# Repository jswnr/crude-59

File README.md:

# Crude-59
A 59-key USB keyboard built using Raspberry Pi Pico

## Images

## Default layout
|         |       |       |       |       |       |       |       |       |       |        |       |                  |
|---------|-------|-------|-------|-------|-------|-------|-------|-------|-------|--------|-------|------------------|
| \`~     | 1! F1 | 2@ F2 | 3# F3 | 4$ F4 | 5% F5 | 6^ F6 | 7& F7 | 8* F8 | 9( F9 | 0) F10 |       |                  |
| Tab     | Q     | W ↑   | E     | R     | T     | Y     | U     | I     | O     | P  F11 |       |                  |
| Esc     | A ←   | S ↓   | D →   | F     | G     | H     | J     | K     | L     | ;: F12 |       |                  | 
| Shift   | Z     | X     | C     | V     | B     | N     | M     | ,<    | .>    | '"     | Enter | Backspace Delete |
| Control | Super | Fn    | Alt   | Space | Space | Alt   | [{    | ]}    | /?    | \\\|   | -_    | =+               |

## Bill of materials
| Name                   | Details                          | Quantity |
|------------------------|----------------------------------|----------|
| 3D printing filament   | PLA was used                     | A/R      |
| Solder                 |                                  | A/R      |
| PCB                    | 1.2 mm thickness                 | 1        |
| Raspberry Pi Pico      |                                  | 1        |
| USB-A to Micro-B cable |                                  | 1        |
| Male pin header        | 2.54 mm pitch, 20 pins           | 2        |
| M2 screw               | Pan head, 6 mm long              | 8        |
| M2 brass insert        | 6 mm long, 3.5 mm outer diameter | 8        |
| Cherry MX switch       |                                  | 59       |
| 1N4148 diode           |                                  | 59       |

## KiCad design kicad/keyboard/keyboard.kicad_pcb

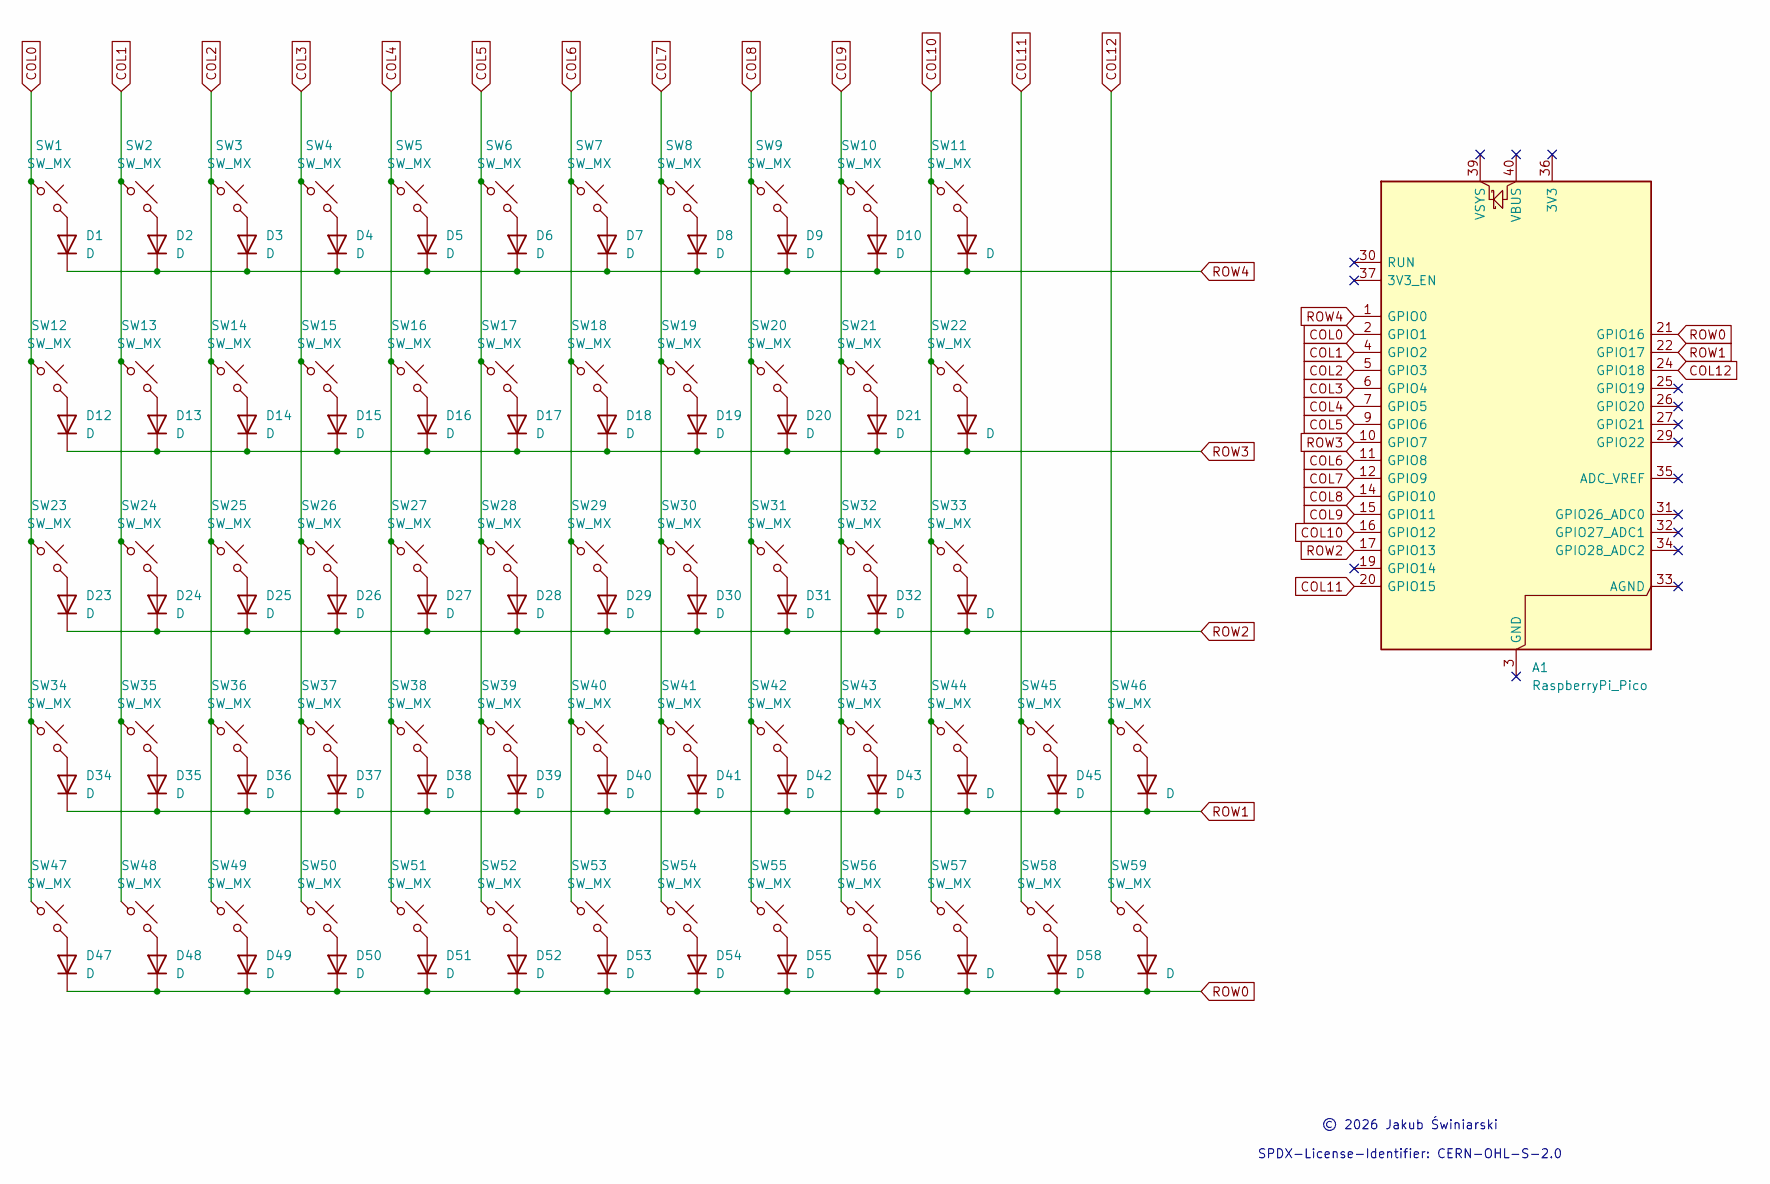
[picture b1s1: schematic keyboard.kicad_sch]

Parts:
A1: RaspberryPi_Pico; RaspberryPi_Pico_Common_THT
D1, D2, D3, D4, D5, D6, D7, D8, D9, D10, D11, D12, D13, D14, D15, D16, D17, D18, D19, D20, D21, D22, D23, D24, D25, D26, D27, D28, D29, D30, D31, D32, D33, D34, D35, D36, D37, D38, D39, D40, D41, D42, D43, D44, D45, D46, D47, D48, D49, D50, D51, D52, D53, D54, D55, D56, D57, D58, D59: D; D_DO-35_SOD27_P7.62mm_Horizontal
SW1, SW2, SW3, SW4, SW5, SW6, SW7, SW8, SW9, SW10, SW11, SW12, SW13, SW14, SW15, SW16, SW17, SW18, SW19, SW20, SW21, SW22, SW23, SW24, SW25, SW26, SW27, SW28, SW29, SW30, SW31, SW32, SW33, SW34, SW35, SW36, SW37, SW38, SW39, SW40, SW41, SW42, SW43, SW44, SW45, SW46, SW47, SW48, SW49, SW50, SW51, SW52, SW53, SW54, SW55, SW56, SW57, SW58, SW59: SW_MX; SW_Cherry_MX_1.00u_PCB

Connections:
COL0: A1.2 (GPIO1), SW1.1, SW12.1, SW23.1, SW34.1, SW47.1
COL1: A1.4 (GPIO2), SW2.1, SW13.1, SW24.1, SW35.1, SW48.1
COL2: A1.5 (GPIO3), SW3.1, SW14.1, SW25.1, SW36.1, SW49.1
COL3: A1.6 (GPIO4), SW4.1, SW15.1, SW26.1, SW37.1, SW50.1
COL4: A1.7 (GPIO5), SW5.1, SW16.1, SW27.1, SW38.1, SW51.1
COL5: A1.9 (GPIO6), SW6.1, SW17.1, SW28.1, SW39.1, SW52.1
COL6: A1.11 (GPIO8), SW7.1, SW18.1, SW29.1, SW40.1, SW53.1
COL7: A1.12 (GPIO9), SW8.1, SW19.1, SW30.1, SW41.1, SW54.1
COL8: A1.14 (GPIO10), SW9.1, SW20.1, SW31.1, SW42.1, SW55.1
COL9: A1.15 (GPIO11), SW10.1, SW21.1, SW32.1, SW43.1, SW56.1
COL10: A1.16 (GPIO12), SW11.1, SW22.1, SW33.1, SW44.1, SW57.1
COL11: A1.20 (GPIO15), SW45.1, SW58.1
COL12: A1.24 (GPIO18), SW46.1, SW59.1
unnamed: D1.2 (A), SW1.2
unnamed: D2.2 (A), SW2.2
unnamed: D3.2 (A), SW3.2
unnamed: D4.2 (A), SW4.2
unnamed: D5.2 (A), SW5.2
unnamed: D6.2 (A), SW6.2
unnamed: D7.2 (A), SW7.2
unnamed: D8.2 (A), SW8.2
unnamed: D9.2 (A), SW9.2
unnamed: D10.2 (A), SW10.2
unnamed: D11.2 (A), SW11.2
unnamed: D12.2 (A), SW12.2
unnamed: D13.2 (A), SW13.2
unnamed: D14.2 (A), SW14.2
unnamed: D15.2 (A), SW15.2
unnamed: D16.2 (A), SW16.2
unnamed: D17.2 (A), SW17.2
unnamed: D18.2 (A), SW18.2
unnamed: D19.2 (A), SW19.2
unnamed: D20.2 (A), SW20.2
unnamed: D21.2 (A), SW21.2
unnamed: D22.2 (A), SW22.2
unnamed: D23.2 (A), SW23.2
unnamed: D24.2 (A), SW24.2
unnamed: D25.2 (A), SW25.2
unnamed: D26.2 (A), SW26.2
unnamed: D27.2 (A), SW27.2
unnamed: D28.2 (A), SW28.2
unnamed: D29.2 (A), SW29.2
unnamed: D30.2 (A), SW30.2
unnamed: D31.2 (A), SW31.2
unnamed: D32.2 (A), SW32.2
unnamed: D33.2 (A), SW33.2
unnamed: D34.2 (A), SW34.2
unnamed: D35.2 (A), SW35.2
unnamed: D36.2 (A), SW36.2
unnamed: D37.2 (A), SW37.2
unnamed: D38.2 (A), SW38.2
unnamed: D39.2 (A), SW39.2
unnamed: D40.2 (A), SW40.2
unnamed: D41.2 (A), SW41.2
unnamed: D42.2 (A), SW42.2
unnamed: D43.2 (A), SW43.2
unnamed: D44.2 (A), SW44.2
unnamed: D45.2 (A), SW45.2
unnamed: D46.2 (A), SW46.2
unnamed: D47.2 (A), SW47.2
unnamed: D48.2 (A), SW48.2
unnamed: D49.2 (A), SW49.2
unnamed: D50.2 (A), SW50.2
unnamed: D51.2 (A), SW51.2
unnamed: D52.2 (A), SW52.2
unnamed: D53.2 (A), SW53.2
unnamed: D54.2 (A), SW54.2
unnamed: D55.2 (A), SW55.2
unnamed: D56.2 (A), SW56.2
unnamed: D57.2 (A), SW57.2
unnamed: D58.2 (A), SW58.2
unnamed: D59.2 (A), SW59.2
ROW0: A1.21 (GPIO16), D47.1 (K), D48.1 (K), D49.1 (K), D50.1 (K), D51.1 (K), D52.1 (K), D53.1 (K), D54.1 (K), D55.1 (K), D56.1 (K), D57.1 (K), D58.1 (K), D59.1 (K)
ROW1: A1.22 (GPIO17), D34.1 (K), D35.1 (K), D36.1 (K), D37.1 (K), D38.1 (K), D39.1 (K), D40.1 (K), D41.1 (K), D42.1 (K), D43.1 (K), D44.1 (K), D45.1 (K), D46.1 (K)
ROW2: A1.17 (GPIO13), D23.1 (K), D24.1 (K), D25.1 (K), D26.1 (K), D27.1 (K), D28.1 (K), D29.1 (K), D30.1 (K), D31.1 (K), D32.1 (K), D33.1 (K)
ROW3: A1.10 (GPIO7), D12.1 (K), D13.1 (K), D14.1 (K), D15.1 (K), D16.1 (K), D17.1 (K), D18.1 (K), D19.1 (K), D20.1 (K), D21.1 (K), D22.1 (K)
ROW4: A1.1 (GPIO0), D1.1 (K), D2.1 (K), D3.1 (K), D4.1 (K), D5.1 (K), D6.1 (K), D7.1 (K), D8.1 (K), D9.1 (K), D10.1 (K), D11.1 (K)

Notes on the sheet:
© 2026 Jakub Świniarski SPDX-License-Identifier: CERN-OHL-S-2.0

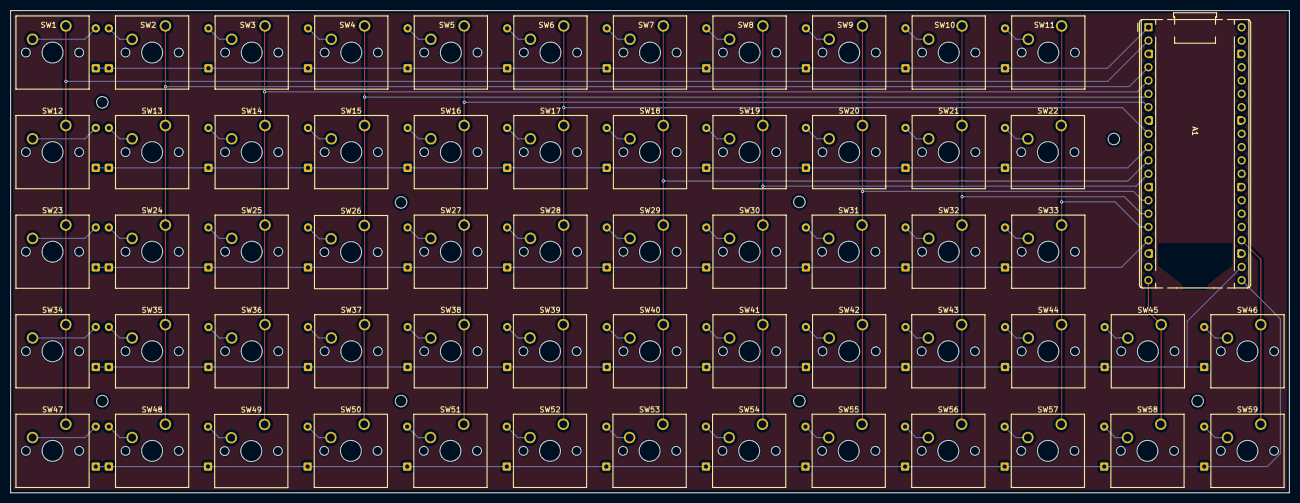
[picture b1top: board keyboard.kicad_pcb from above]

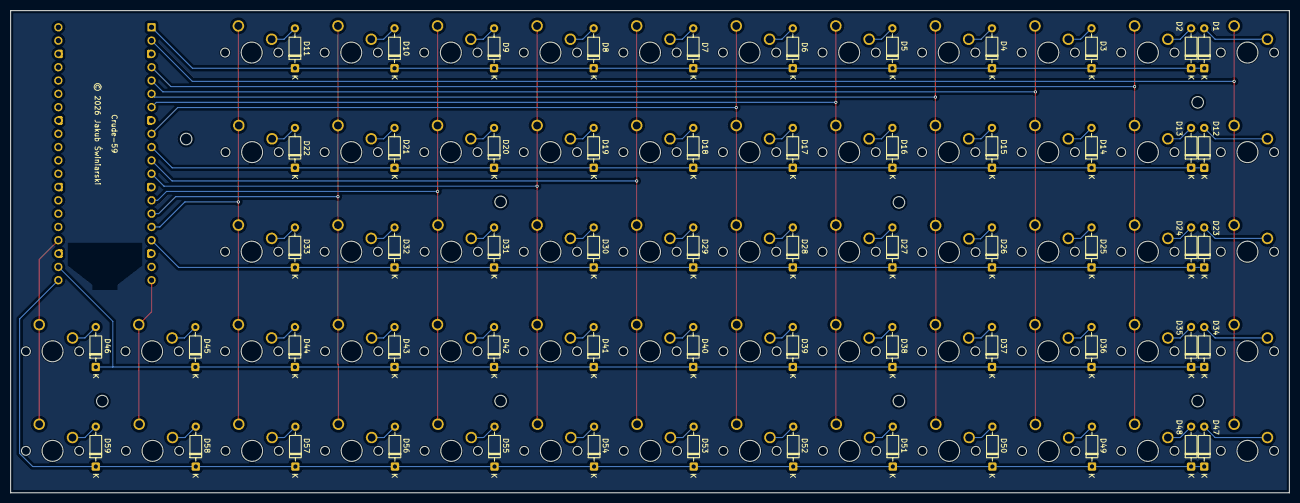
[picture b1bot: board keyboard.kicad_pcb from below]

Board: 2 copper layers, 244.0 x 92.0 mm, 119 parts (59 on the bottom side), 77 nets.

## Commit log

2025-12-04 Simple firmware for a basic keyboard
2025-12-06 Assign footprints
2025-12-08 Connect rows and columns to Pico
2025-12-08 Mounting holes and copper fill
2025-12-08 Update product name
2026-01-19 Add case model
2026-01-20 Add more support
2026-01-20 USB hole improvements
2026-01-20 Configure the model for brass inserts
2026-01-22 Minor adjustments
2026-01-23 Add gussets
2026-01-23 Reduce the size of the rod hole
2026-01-24 Update variable names
2026-01-24 Add keycap model
2026-01-25 Add curvature
2026-01-25 Reduce margin and rod radius, add formula for curve_r
2026-01-27 Add images
2026-01-27 Update images
2026-01-31 Add Fn key and update layout
2026-01-31 Add licenses
2026-01-31 Fix table
2026-02-01 Add BOM
2026-02-02 Add spaces before units
2026-02-03 Modify Fn layout and add layout to README
2026-02-04 Add project name silkscreen and move copyright silkscreen
2026-02-08 Add pin headers to BOM
2026-02-10 Update copyright notices
2026-02-11 Reduce clock frequency
2026-02-11 Disable some clocks
